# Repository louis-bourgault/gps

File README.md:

# custom gps tracker module
aims
- week long battery life for long hikes
- stores in flash, can go to strava afterwards by streaming to my laptop to upoad

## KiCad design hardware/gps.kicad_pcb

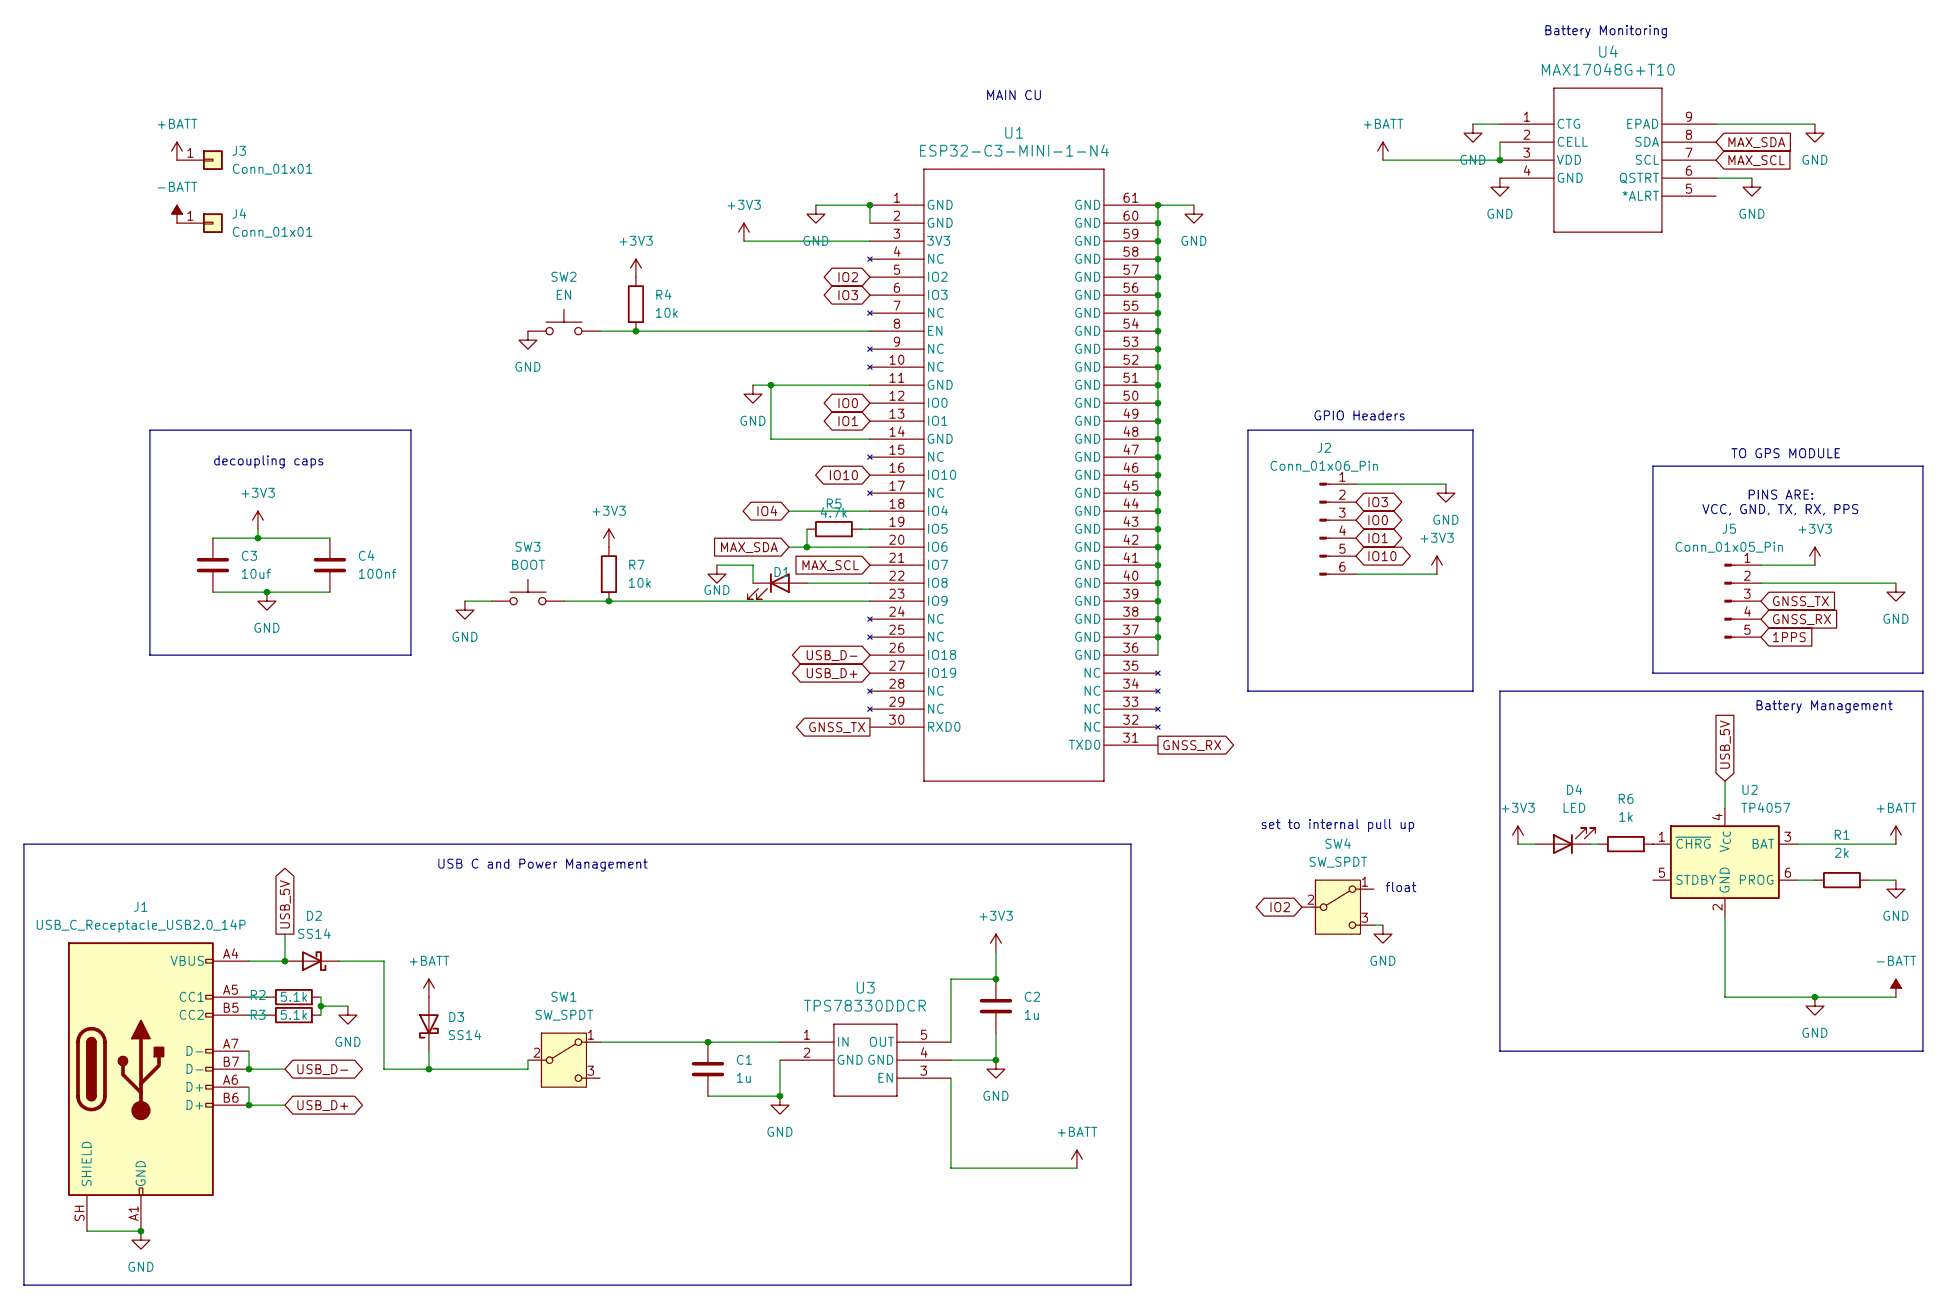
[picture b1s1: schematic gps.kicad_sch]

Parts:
C1, C2: 1u; C_0402_1005Metric
C3: 10uf; C_0402_1005Metric
C4: 100nf; C_0402_1005Metric
D1, D4: LED; LED_0603_1608Metric
D2, D3: SS14; D_SOD-123
J1: USB_C_Receptacle_USB2.0_14P; USB_C_Receptacle_HRO_TYPE-C-31-M-12
J2: Conn_01x06_Pin; PinHeader_1x06_P2.54mm_Vertical
J3, J4: Conn_01x01; TestPoint_Pad_2.5x2.5mm
J5: Conn_01x05_Pin; PinHeader_1x05_P2.54mm_Vertical
R1: 2k; R_0402_1005Metric
R2, R3: 5.1k; R_0402_1005Metric
R4, R7: 10k; R_0402_1005Metric
R5: 4.7k; R_0603_1608Metric
R6: 1k; R_0603_1608Metric
SW1, SW4: SW_SPDT; SW_SPDT_Shouhan_MSK12C02
SW2: EN; SW_Push_SPST_NO_Alps_SKRK
SW3: BOOT; SW_Push_SPST_NO_Alps_SKRK
U1: ESP32-C3-MINI-1-N4; ESP32-C3-MINI-1_EXP
U2: TP4057; TSOT-23-6
U3: TPS78330DDCR; DDC5_TEX
U4: MAX17048G+T10; 21-0168E_T822-3_MXM

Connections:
1PPS: J5.5 (PPS)
+3V3: C2.1, C3.1, C4.1, D4.2 (A), J2.6, J5.1 (VCC), R4.1, R7.1, U1.3 (3V3), U3.5 (OUT)
+BATT: D3.2 (A), J3.1 (Pin_1_1), U2.3 (BAT), U3.3 (EN), U4.2 (CELL), U4.3 (VDD)
-BATT: C1.2, C2.2, C3.2, C4.2, D1.1 (K), J1.A1 (GND), J1.A12 (GND), J1.B1 (GND), J1.B12 (GND), J1.SH (SHIELD), J2.1, J4.1 (Pin_1_1), J5.2 (GND), R1.2, R2.2, R3.2, SW2.1, SW3.1, SW4.3 (C), SW4.SH, U1.1 (GND), U1.2 (GND), U1.11 (GND), U1.14 (GND), U1.36 (GND), U1.37 (GND), U1.38 (GND), U1.39 (GND), U1.40 (GND), U1.41 (GND), U1.42 (GND), U1.43 (GND), U1.44 (GND), U1.45 (GND), U1.46 (GND), U1.47 (GND), U1.48 (GND), U1.49 (GND), U1.50 (GND), U1.51 (GND), U1.52 (GND), U1.53 (GND), U1.54 (GND), U1.55 (GND), U1.56 (GND), U1.57 (GND), U1.58 (GND), U1.59 (GND), U1.60 (GND), U1.61 (GND), U2.2 (GND), U3.2 (GND), U3.4 (GND), U4.1 (CTG), U4.4 (GND), U4.6 (QSTRT), U4.9 (EPAD)
GNSS_RX: J5.4 (RX), U1.31 (TXD0)
GNSS_TX: J5.3 (TX), U1.30 (RXD0)
IO0: J2.3, U1.12 (IO0)
IO1: J2.4, U1.13 (IO1)
IO2: SW4.2 (B), U1.5 (IO2)
IO3: J2.2, U1.6 (IO3)
IO4: U1.18 (IO4)
IO10: J2.5, U1.16 (IO10)
MAX_SCL: U1.21 (IO7), U4.7 (SCL)
MAX_SDA: R5.1, U1.20 (IO6), U4.8 (SDA)
unnamed: D1.2 (A), U1.22 (IO8)
unnamed: D2.1 (K), D3.1 (K), SW1.2 (B)
unnamed: D4.1 (K), R6.1
unnamed: J1.A5 (CC1), R2.1
unnamed: J1.B5 (CC2), R3.1
unnamed: C1.1, SW1.1 (A), U3.1 (IN)
unnamed: R4.2, SW2.2, U1.8 (EN)
unnamed: R5.2, U1.19 (IO5)
unnamed: R7.2, SW3.2, U1.23 (IO9)
unnamed: R1.1, U2.6 (PROG)
unnamed: R6.2, U2.1 (~CHRG)
USB_5V: D2.2 (A), J1.A4 (VBUS), J1.A9 (VBUS), J1.B4 (VBUS), J1.B9 (VBUS), U2.4 (V_{CC})
USB_D+: J1.A6 (D+), J1.B6 (D+), U1.27 (IO19)
USB_D-: J1.A7 (D-), J1.B7 (D-), U1.26 (IO18)

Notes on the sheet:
USB C and Power Management
TO GPS MODULE
Battery Management
Battery Monitoring
decoupling caps
MAIN CU
float
set to internal pull up
PINS ARE: VCC, GND, TX, RX, PPS
GPIO Headers

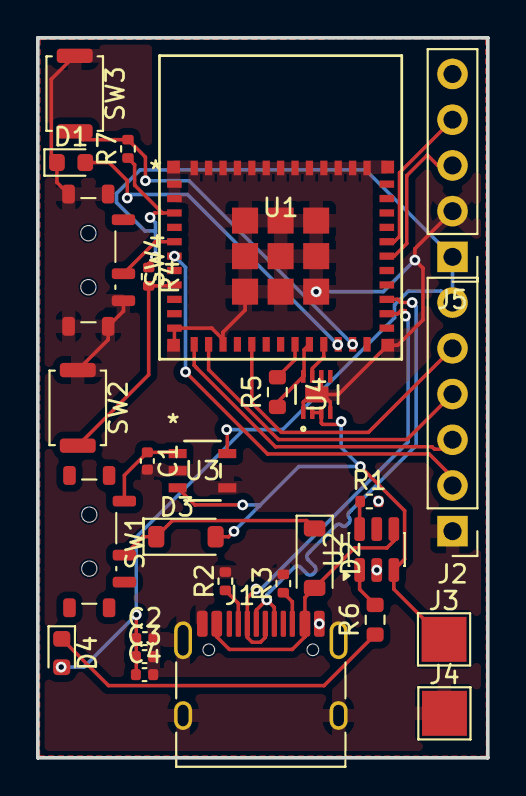
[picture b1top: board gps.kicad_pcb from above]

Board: 2 copper layers, 25.0 x 40.0 mm, 28 parts (0 on the bottom side), 26 nets.

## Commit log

2026-06-24 init esp-idf project (also old software)
2026-06-24 clean up tracked build artifacts
2026-06-24 very simple start to the c code
2026-06-26 feat: placed features on hardware board
2026-06-27 feat: wire pcb
